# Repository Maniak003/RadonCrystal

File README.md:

# RadonCrystal
Fork Radon project: https://github.com/radon-lab/ArDos_with_RADON/

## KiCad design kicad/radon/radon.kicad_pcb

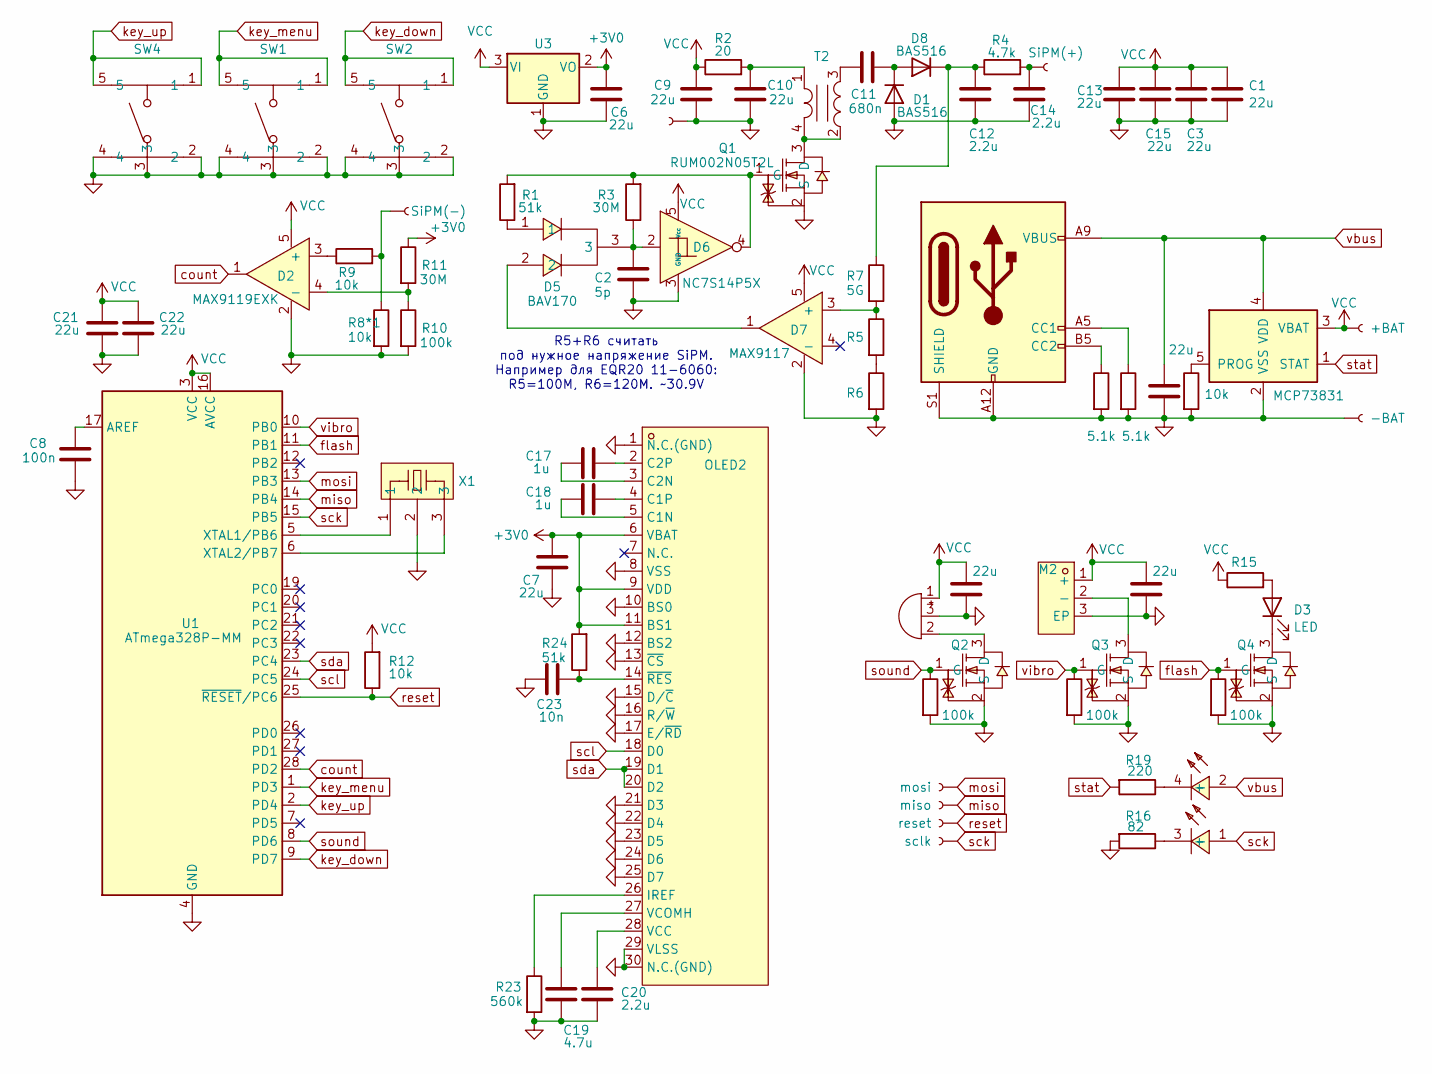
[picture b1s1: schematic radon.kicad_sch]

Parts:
BZ1: Buzzer; Buzzer55x55
C1, C3, C4, C5, C6, C7, C9, C10, C13, C15, C16, C21, C22: 22u; C_0402_1005Metric
C2: 5p; C_0402_1005Metric
C8: 100n; C_0402_1005Metric
C11: 680n; C_0402_1005Metric
C12, C14: 2.2u; C_0603_1608Metric
C17, C18: 1u; C_0402_1005Metric
C19: 4.7u; C_0402_1005Metric
C20: 2.2u; C_0402_1005Metric
C23: 10n; C_0402_1005Metric
D1, D8: BAS516; D_SOD-523
D2: MAX9119EXK; SOT-353_SC-70-5
D3: LED; D_0805_2012Metric
D5: BAV170; SOT-523; LCSC Part C68970
D6: NC7S14P5X; SC-70-5_L2.1-W1.3-P0.65-LS2.2-BR
D7: MAX9117; SC-70-5_L2.1-W1.3-P0.65-LS2.2-BR
J1: SiPM(+); ConnMini
J2: SiPM(-); ConnMini
J3: USB_C_Receptacle_PowerOnly_6P; USB_C_Receptacle_GCT_USB4135-GF-A_6P_TopMnt_Horizontal
J5: Conn; ConnMini
J7: +BAT; ConnMini
J8: -BAT; ConnMini
J9: mosi; ConnMini
J10: miso; ConnMini
J11: sclk; ConnMini
J12: reset; ConnMini
LED1: LTST-C195KGJRKT; LED-ARRAY-SMD_0603-4P-L1.6-W1.5-BR-RD; LCSC Part C125104
M2: Z3OC1T8219731; VIBRATING-MOTOR-SMD_3P-C9900001680; LCSC Part C2894731
OLED2: N096-2864KSWEG01-H30; OLED_0.96-30P-P0.70-12864; LCSC Part C2890596
Q1, Q2, Q3, Q4: RUM002N05T2L; SOT-723-3_L1.2-W0.8-LS1.20-BR; LCSC Part C510347
R1, R24: 51k; R_0402_1005Metric
R2: 20; R_0402_1005Metric
R3, R11: 30M; R_0402_1005Metric
R4: 4.7k; R_0402_1005Metric
R5: 300k; R_0402_1005Metric
R6: 10M; R_0402_1005Metric
R7: 5G; R_0805_2012Metric
R8*1, R9, R12, R14: 10k; R_0402_1005Metric
R10, R20, R21, R22: 100k; R_0402_1005Metric
R15: 51; R_0402_1005Metric
R16: 82; R_0402_1005Metric
R17, R18: 5.1k; R_0402_1005Metric
R19: 220; R_0402_1005Metric
R23: 560k; R_0402_1005Metric
SW1, SW2, SW4: KMS231GLFS; SW-SMD_KMS2XXGXXX; LCSC Part C221701
T2: ATB322515-0110-T000; XFMR-SMD_ATB322515-0110-T000; LCSC Part C415291
U1: ATmega328P-MM; QFN-28-1EP_4x4mm_P0.45mm_EP2.4x2.4mm
U2: MCP73831; SOT-23-5
U3: MCP1700x-300xxTT; SOT-23
X1: CSTCE16M0V53-R0; Resonator_SMD_Murata_CSTxExxV-3Pin_3.0x1.1mm; LCSC Part C32180

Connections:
+3V0: C6.1, C7.1, OLED2.6 (VBAT), OLED2.9 (VDD), OLED2.11 (BS1), R11.1, R24.2, U3.2 (VO)
GND: BZ1.3 (GND), C1.2, C2.1, C3.1, C4.2, C5.2, C6.2, C7.2, C8.2, C9.2, C10.2, C12.1, C13.1, C14.1, C15.1, C16.2, C19.2, C20.2, C21.2, C22.2, C23.1, D1.2 (A), D2.2, D6.3 (GND), D7.2, J3.A12 (GND), J3.B12 (GND), J3.S1 (SHIELD), J5.1, J8.1, M2.3 (EP), OLED2.1 (N.C.(GND)), OLED2.8 (VSS), OLED2.10 (BS0), OLED2.12 (BS2), OLED2.13 (~CS), OLED2.15 (D/~C), OLED2.16 (R/~W), OLED2.17 (E/~RD), OLED2.21 (D3), OLED2.22 (D4), OLED2.23 (D5), OLED2.24 (D6), OLED2.25 (D7), OLED2.29 (VLSS), OLED2.30 (N.C.(GND)), Q1.2 (S), Q2.2 (S), Q3.2 (S), Q4.2 (S), R6.2, R8*1.2, R10.2, R14.2, R16.2, R17.2, R18.2, R20.2, R21.2, R22.2, R23.2, SW1.2, SW1.3, SW1.4, SW2.2, SW2.3, SW2.4, SW4.2, SW4.3, SW4.4, U1.4 (GND), U1.18 (GND), U1.29 (GND), U2.2 (VSS), U3.1 (GND), X1.2
unnamed: BZ1.2 (+), Q2.3 (D)
unnamed: C2.2, D5.3, D6.2, R3.1
unnamed: C10.1, R2.2, T2.1
unnamed: C11.1, T2.3
unnamed: C14.2, J1.1, R4.2
unnamed: C11.2, D1.1 (K), D8.2 (A)
unnamed: D2.3 (+), R9.1
unnamed: D2.4 (-), R10.1, R11.2
unnamed: D3.2 (A), R15.2
unnamed: D3.1 (K), Q4.3 (D)
unnamed: D5.1, R1.1
unnamed: D5.2, D7.1
unnamed: D7.3 (+), R5.1, R7.2
unnamed: C12.2, D8.1 (K), R4.1, R7.1
unnamed: J2.1, R8*1.1, R9.2
unnamed: J3.A5 (CC1), R17.1
unnamed: J3.B5 (CC2), R18.1
unnamed: LED1.3 (-), R16.1
unnamed: LED1.4 (-), R19.1
unnamed: M2.2 (-), Q3.3 (D)
unnamed: C18.2, OLED2.5 (C1N)
unnamed: C18.1, OLED2.4 (C1P)
unnamed: C17.2, OLED2.3 (C2N)
unnamed: C17.1, OLED2.2 (C2P)
unnamed: OLED2.26 (IREF), R23.1
unnamed: C20.1, OLED2.28 (VCC)
unnamed: C19.1, OLED2.27 (VCOMH)
unnamed: C23.2, OLED2.14 (~RES), R24.1
unnamed: Q1.3 (D), T2.2, T2.4
unnamed: D6.4, Q1.1 (G), R1.2, R3.2
unnamed: R5.2, R6.1
unnamed: C8.1, U1.17 (AREF)
unnamed: U1.5 (XTAL1/PB6), X1.1
unnamed: U1.6 (XTAL2/PB7), X1.3
unnamed: R14.1, U2.5 (PROG)
VCC: BZ1.1 (-), C1.1, C3.2, C4.1, C5.1, C9.1, C13.2, C15.2, C21.1, C22.1, D2.5, D6.5 (Vcc), D7.5, J7.1, M2.1 (+), R2.1, R12.2, R15.1, U1.3 (VCC), U1.16 (AVCC), U2.3 (VBAT), U3.3 (VI)
count: D2.1, U1.28 (PD2)
flash: Q4.1 (G), R22.1, U1.11 (PB1)
key_down: SW2.1, SW2.5, U1.9 (PD7)
key_menu: SW1.1, SW1.5, U1.1 (PD3)
key_up: SW4.1, SW4.5, U1.2 (PD4)
miso: J10.1, U1.14 (PB4)
mosi: J9.1, U1.13 (PB3)
reset: J12.1, R12.1, U1.25 (~RESET/PC6)
sck: J11.1, LED1.1 (+), U1.15 (PB5)
scl: OLED2.18 (D0), U1.24 (PC5)
sda: OLED2.19 (D1), OLED2.20 (D2), U1.23 (PC4)
sound: Q2.1 (G), R20.1, U1.8 (PD6)
stat: R19.2, U2.1 (STAT)
vbus: C16.1, J3.A9 (VBUS), J3.B9 (VBUS), LED1.2 (+), U2.4 (VDD)
vibro: Q3.1 (G), R21.1, U1.10 (PB0)

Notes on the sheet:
R5+R6 считать под нужное напряжение SiPM. Например для EQR20 11-6060: R5=100M, R6=120M. ~30.9V

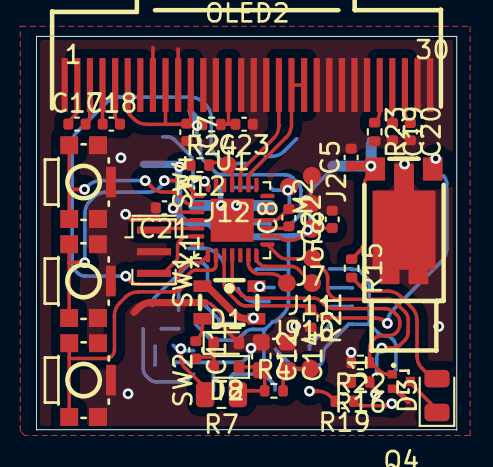
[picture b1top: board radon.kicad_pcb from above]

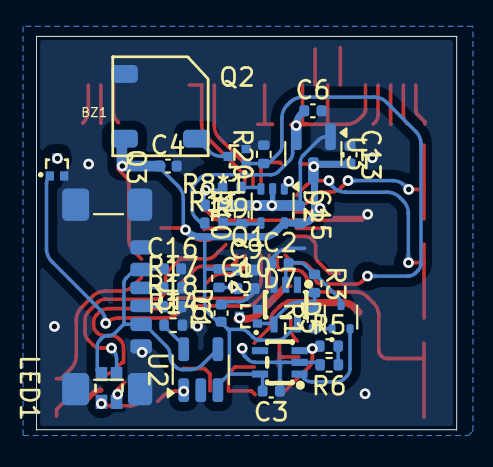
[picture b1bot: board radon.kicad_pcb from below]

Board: 2 copper layers, 23.3 x 21.9 mm, 79 parts (35 on the bottom side), 53 nets.

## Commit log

2026-02-08 новый файл: FreeCAD/RadonCase.FCStd новый файл: FreeCAD/RadonCase.stl новый файл: kicad/radon/fp-info-cache новый файл: kicad/radon/radon.kicad_pcb новый файл: kicad/radon/radon.kicad_prl новый файл: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
2026-02-08 изменено: Arduino/ArDos_with_RADON/connection.h изменено: FreeCAD/RadonCase.FCStd изменено: FreeCAD/RadonCase.stl
2026-02-08 изменено: FreeCAD/RadonCase.FCStd изменено: FreeCAD/RadonCase.stl
2026-02-08 удалено: FreeCAD/RadonCase.FCStd1
